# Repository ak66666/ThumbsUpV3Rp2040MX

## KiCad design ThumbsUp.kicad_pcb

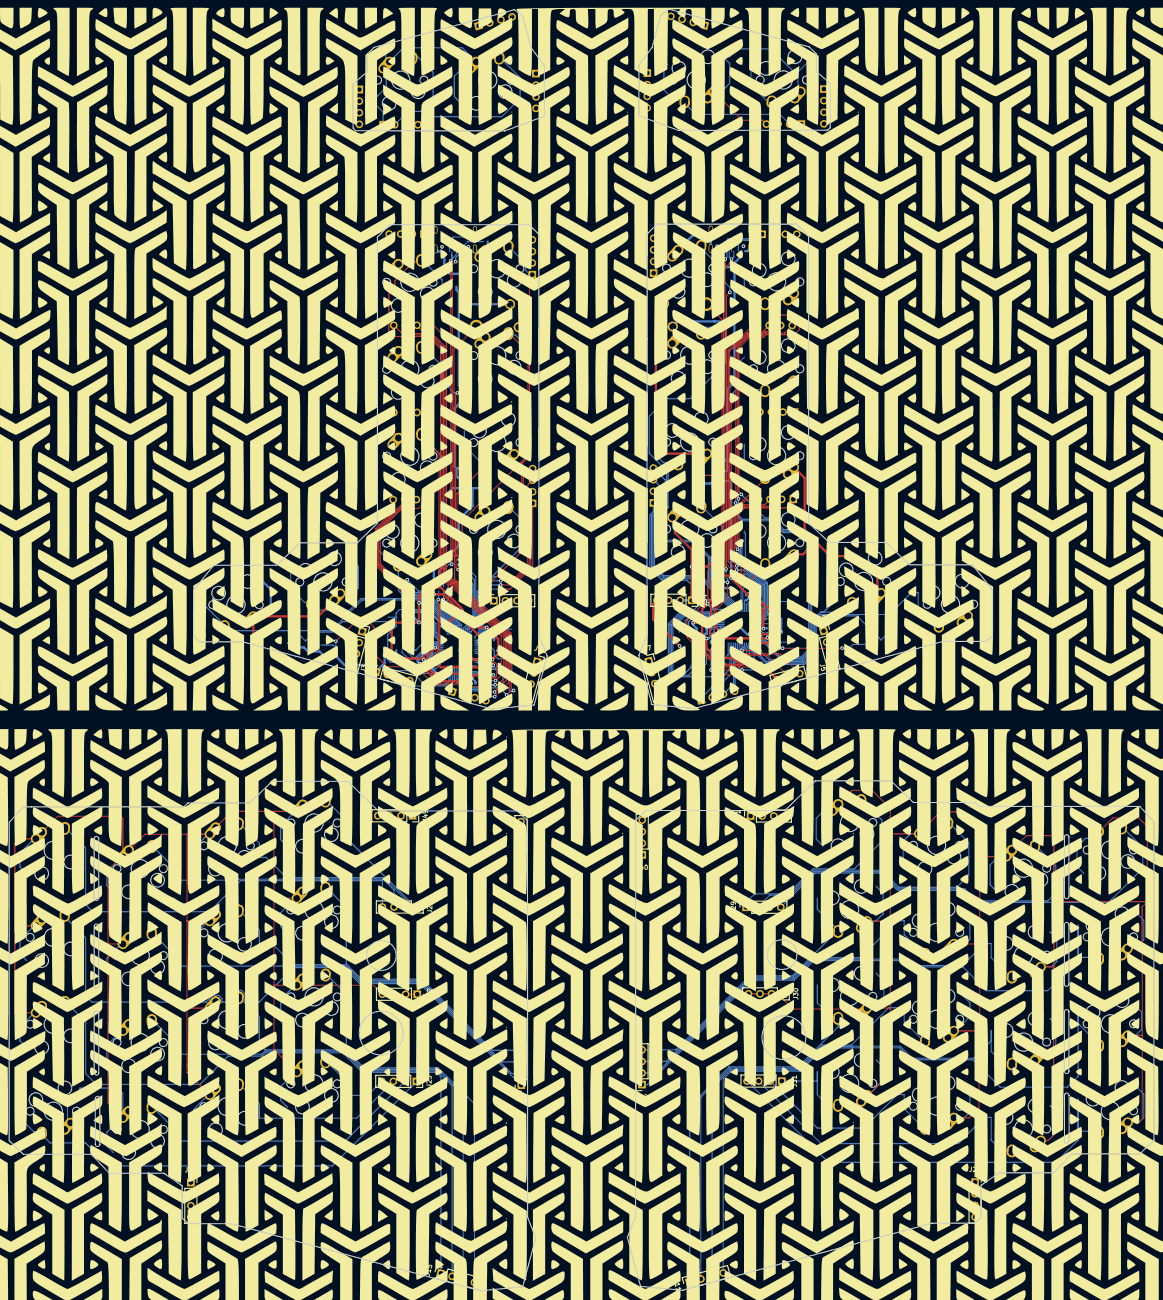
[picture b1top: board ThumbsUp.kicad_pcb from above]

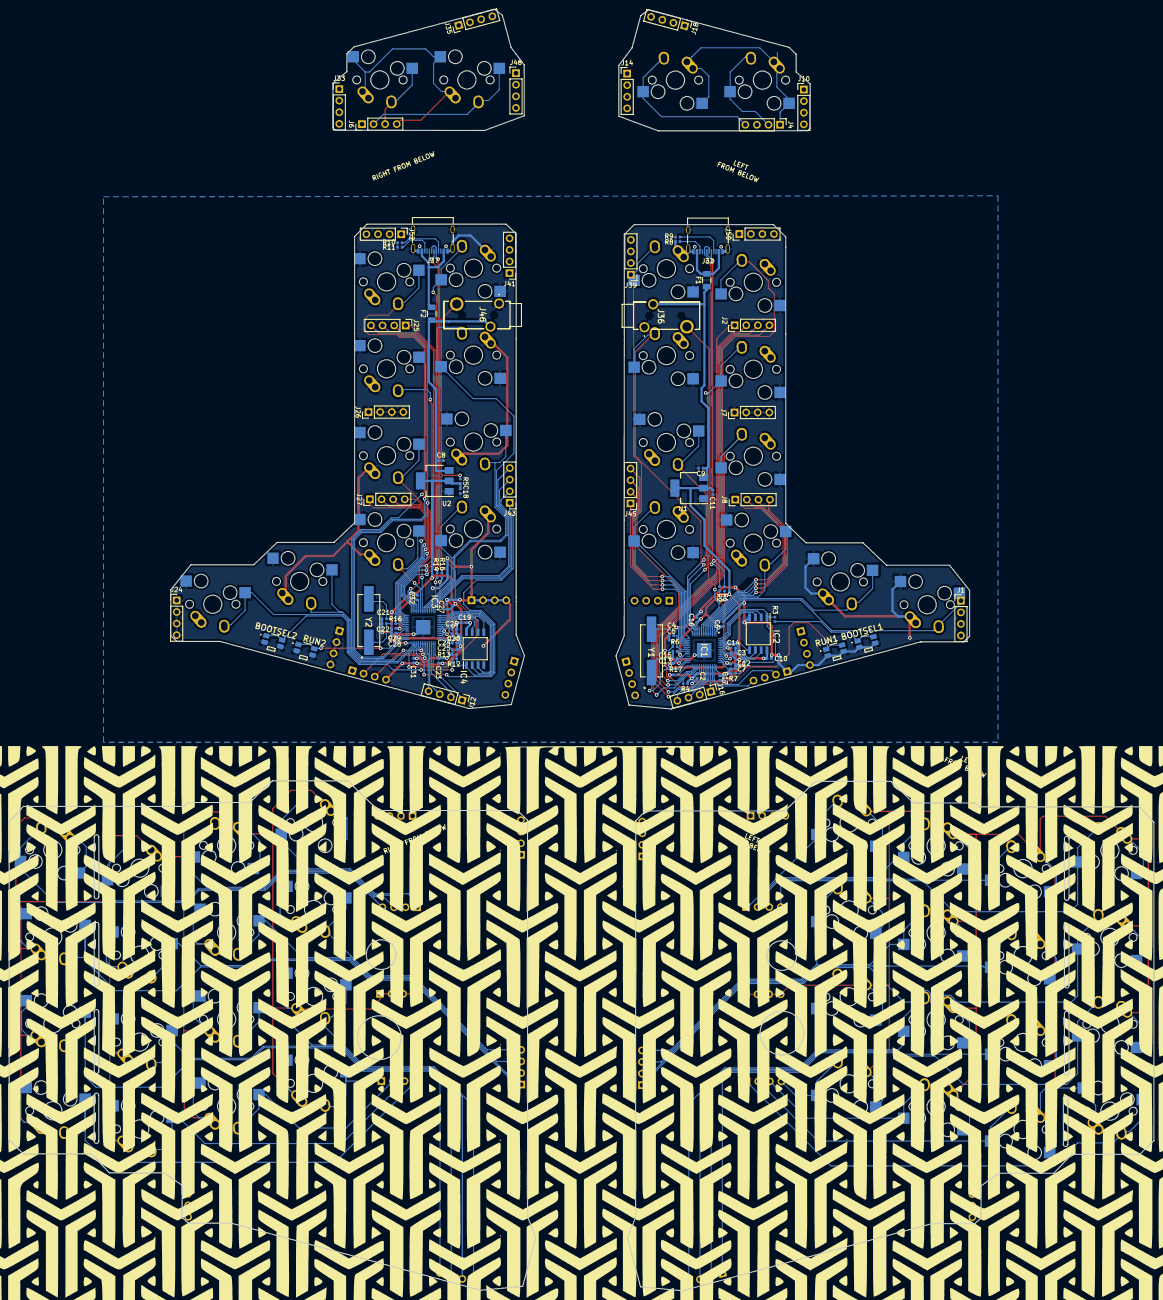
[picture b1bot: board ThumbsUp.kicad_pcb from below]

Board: 2 copper layers, 250.9 x 280.9 mm, 169 parts (89 on the bottom side), 138 nets.

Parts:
BOOTSEL1, BOOTSEL2: TL1016AAF220QG
C2, C6, C7, C10, C13, C14, C15, C16, C17, C19, C23, C25, C26, C27, C28, C29, C31, C32: 0.1uF; C_0402_1005Metric
C3, C12, C20, C24: 1uF; C_0402_1005Metric
C4, C5, C21, C22: 27pF; C_0402_1005Metric
C8, C9, C11, C18: 10uF; C_0402_1005Metric
F1, F2: Polyfuse; Fuse_1206_3216Metric
IC1, IC3: RP2040; QFN40P700X700X90-57N-D
IC2, IC4: W25Q128JVSIM; SOIC127P790X216-8N
J1, J2, J4, J6, J7, J8, J24, J25, J26, J27: Conn_01x04_Male; PinHeader_1x04_P2.54mm_Vertical
J3, J5, J20, J21, J22, J23, J28, J29, J30, J31: Conn_01x04_Female; PinSocket_1x04_P2.54mm_Vertical
J9, J11, J13, J15, J17, J19, J34, J38, J40, J42, J44, J47, J49, J51: Raiser_Female; PinSocket_1x04_P2.54mm_Vertical
J10, J12, J14, J16, J18, J33, J35, J39, J41, J43, J45, J48, J50, J52: Raiser_Male; PinHeader_1x04_P2.54mm_Vertical
J32, J37: USB_C_Receptacle_USB2.0; USB_C_Receptacle_Palconn_UTC16-G
J36, J46: STX-3501-3N; STX35013N
MX1: SwESC; MX-1U-NoLED_HotSwap
MX2: SwTAB; MX-1U-NoLED_HotSwap
MX3: SwLCTL; MX-1U-NoLED_HotSwap
MX4: SwQ; MX-1U-NoLED_HotSwap
MX5: SwA; MX-1U-NoLED_HotSwap
MX6: SwZ; MX-1U-NoLED_HotSwap
MX7: SwW; MX-1U-NoLED_HotSwap
MX8: SwS; MX-1U-NoLED_HotSwap
MX9: SwX; MX-1U-NoLED_HotSwap
MX10: SwLWIN; MX-1U-NoLED_HotSwap
MX11: SwE; MX-1U-NoLED_HotSwap
MX12: SwD; MX-1U-NoLED_HotSwap
MX13: SwC; MX-1U-NoLED_HotSwap
MX14: SwLALT; MX-1U-NoLED_HotSwap
MX15: SwR; MX-1U-NoLED_HotSwap
MX16: SwF; MX-1U-NoLED_HotSwap
MX17: SwV; MX-1U-NoLED_HotSwap
MX18: SwLMOD; MX-1U-NoLED_HotSwap
MX19: SwT; MX-1U-NoLED_HotSwap
MX20: SwG; MX-1U-NoLED_HotSwap
MX21: SwB; MX-1U-NoLED_HotSwap
MX22: SwLSHFT; MX-1U-NoLED_HotSwap
MX23: SwY; MX-1U-NoLED_HotSwap
MX24: SwH; MX-1U-NoLED_HotSwap
MX25: SwN; MX-1U-NoLED_HotSwap
MX26: SwRSHFT; MX-1U-NoLED_HotSwap
MX27: SwU; MX-1U-NoLED_HotSwap
MX28: SwJ; MX-1U-NoLED_HotSwap
MX29: SwM; MX-1U-NoLED_HotSwap
MX30: SwRMOD; MX-1U-NoLED_HotSwap
MX31: SwI; MX-1U-NoLED_HotSwap
MX32: SwK; MX-1U-NoLED_HotSwap
MX33: SwCOMMA; MX-1U-NoLED_HotSwap
MX34: SwRALT; MX-1U-NoLED_HotSwap
MX35: SwO; MX-1U-NoLED_HotSwap
MX36: SwL; MX-1U-NoLED_HotSwap
MX37: SwDOT; MX-1U-NoLED_HotSwap
MX38: SwMENU; MX-1U-NoLED_HotSwap
MX39: SwP; MX-1U-NoLED_HotSwap
MX40: SwCOLON; MX-1U-NoLED_HotSwap
MX41: Sw?; MX-1U-NoLED_HotSwap
MX42: SwBKSP; MX-1U-NoLED_HotSwap
MX43: SwENTER; MX-1U-NoLED_HotSwap
MX44: SwRCTRL; MX-1U-NoLED_HotSwap
MX45: SwGrave; MX-1U-NoLED_HotSwap
MX46: Sw1; MX-1U-NoLED_HotSwap
MX47: Sw2; MX-1U-NoLED_HotSwap
MX48: Sw3; MX-1U-NoLED_HotSwap
MX49: Sw4; MX-1U-NoLED_HotSwap
MX50: Sw5; MX-1U-NoLED_HotSwap
MX51: Sw6; MX-1U-NoLED_HotSwap
MX52: Sw7; MX-1U-NoLED_HotSwap
MX53: Sw8; MX-1U-NoLED_HotSwap
MX54: Sw9; MX-1U-NoLED_HotSwap
MX55: Sw0; MX-1U-NoLED_HotSwap
MX56: SwDEL; MX-1U-NoLED_HotSwap
R1, R2, R14, R15: 27.4; R_0402_1005Metric
R3, R12: 10k; R_0402_1005Metric
R4, R5, R17: 5.1K; R_0402_1005Metric
R6, R16: 1k; R_0402_1005Metric
R7, R13: DNF; R_0402_1005Metric
R8, R9, R10, R11: 5.1k; R_0402_1005Metric
RUN1, RUN2: TL1016AAF220QG
U1, U2: NCP1117-3.3_SOT223; SOT-223-3_TabPin2
Y1, Y2: ABLS-12.000MHZ-B4-T; HC%2f49US-(AT49)_1

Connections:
+1V1: C12.1, C13.1, C14.1, C24.1, C26.1, C28.1, IC1.23, IC1.45, IC1.50, IC3.23, IC3.45, IC3.50
+3V3: C2.1, C3.1, C6.1, C7.1, C10.1, C11.1, C15.1, C16.1, C17.1, C18.1, C19.1, C20.1, C23.1, C25.1, C27.1, C29.1, C31.1, C32.1, IC1.1, IC1.10, IC1.22, IC1.33, IC1.42, IC1.43, IC1.44, IC1.48, IC1.49, IC2.8, IC3.1, IC3.10, IC3.22, IC3.33, IC3.42, IC3.43, IC3.44, IC3.48, IC3.49, IC4.8, R4.1, R5.2, R7.2, R13.2, R17.1, U1.2, U2.2
+5VA: F1.2, F2.2, J32.A4, J32.A9, J32.B4, J32.B9, J37.A4, J37.A9, J37.B4, J37.B9
D+: J32.A6, J32.B6, R2.2
D-: J32.A7, J32.B7, R1.2
K_0: IC3.14, J25.2
K_1: IC1.31, J2.3
K_2: IC1.34, J2.2
K_3: IC1.35, J2.1
K_4: IC1.27, MX49.2
K_5: IC1.28, J39.1, MX50.2
K_6: IC3.12, MX51.2
K_7: IC3.35, MX52.2
K_8: IC3.28, J25.4
K_9: IC3.27, J25.3
K_A: IC1.38, J16.2
K_B: IC1.14, MX21.2
K_BSPC: IC3.34, J43.1
K_C: IC1.5, J8.4
K_COMM: IC3.18, J27.1
K_D: IC1.36, J16.4
K_DEL: IC3.13, J25.1
K_DOT: IC3.17, J27.2
K_E: IC1.15, J45.4
K_ENT: IC3.38, J12.4
K_ESC: IC1.18, J45.1
K_F: IC1.9, MX16.2
K_G: IC1.13, MX20.2
K_GRAVE: IC1.30, J2.4
K_H: IC3.6, MX24.2
K_I: IC3.4, J43.4
K_J: IC3.11, MX28.2
K_K: IC3.41, J12.1
K_L: IC3.40, J12.2
K_LALT: IC1.3, MX14.2
K_LCTL: IC1.8, J8.1
K_LSFT: IC1.41, J3.2
K_LWR: IC3.36, J5.2
K_M: IC3.9, MX29.2
K_MNU: IC3.31, MX38.2
K_N: IC3.7, MX25.2
K_O: IC3.3, J43.3
K_P: IC3.2, J43.2
K_Q: IC1.17, J45.2
K_R: IC1.11, MX15.2
K_RALT: IC3.30, MX34.2
K_RCTL: IC3.15, J27.4
K_RSE: IC1.40, J3.4
K_RSFT: IC3.37, J5.3
K_S: IC1.37, J16.3
K_SEMICOL: IC3.39, J12.3
K_SLASH: IC3.16, J27.3
K_T: IC1.12, MX19.2
K_TAB: IC1.39, J16.1
K_U: IC3.8, MX27.2
K_V: IC1.4, MX17.2
K_W: IC1.16, J45.3
K_WIN: IC1.2, J1.1, MX10.2
K_X: IC1.6, J8.3
K_Y: IC3.5, MX23.2
K_Z: IC1.7, J8.2
L-BASE: BOOTSEL1.3, BOOTSEL1.4, BOOTSEL2.3, BOOTSEL2.4, C2.2, C3.2, C4.2, C5.2, C6.2, C7.2, C8.2, C9.2, C10.2, C11.2, C12.2, C13.2, C14.2, C15.2, C16.2, C17.2, C18.2, C19.2, C20.2, C21.2, C22.2, C23.2, C24.2, C25.2, C26.2, C27.2, C28.2, C29.2, C31.2, C32.2, IC1.19, IC1.57, IC2.4, IC3.19, IC3.29, IC3.57, IC4.4, J3.1, J5.4, J7.1, J7.2, J7.3, J7.4, J9.4, J19.1, J19.2, J19.3, J19.4, J24.1, J24.2, J24.3, J24.4, J26.1, J26.2, J26.3, J26.4, J32.A1, J32.A12, J32.B1, J32.B12, J32.S1, J34.1, J34.2, J34.3, J34.4, J36.1, J37.A1, J37.A12, J37.B1, J37.B12, J37.S1, J46.1, MX10.1, MX14.1, MX15.1, MX16.1, MX17.1, MX19.1, MX20.1, MX21.1, MX23.1, MX24.1, MX25.1, MX27.1, MX28.1, MX29.1, MX34.1, MX38.1, MX49.1, MX50.1, MX51.1, MX52.1, R8.2, R9.1, R10.2, R11.1, RUN1.3, RUN1.4, RUN2.3, RUN2.4, U1.1, U2.1
L-RING1: C8.1, C9.1, F1.1, F2.1, J36.3, J46.3, U1.3, U2.3
L-TIP: IC1.32, J36.2, R4.2
unnamed: BOOTSEL1.1, BOOTSEL1.2, R3.1
unnamed: BOOTSEL2.1, BOOTSEL2.2, R12.1
unnamed: C5.1, R6.2, Y1.1
unnamed: C22.1, R16.2, Y2.1
unnamed: IC1.26, RUN1.1, RUN1.2
unnamed: IC1.29, R17.2
unnamed: IC1.46, R1.1
unnamed: IC1.47, R2.1
unnamed: IC3.26, RUN2.1, RUN2.2
unnamed: IC3.46, R15.1
unnamed: IC3.47, R14.1
unnamed: J4.1, MX18.1, MX22.1
unnamed: J4.2, MX22.2
unnamed: J4.4, MX18.2
unnamed: J6.2, MX30.2
unnamed: J6.3, MX26.2
unnamed: J6.4, MX26.1, MX30.1
unnamed: J11.1, MX32.2
unnamed: J11.2, MX36.2
unnamed: J11.3, MX40.2
unnamed: J11.4, MX43.2
unnamed: J15.1, MX2.2
unnamed: J15.2, MX5.2
unnamed: J15.3, MX8.2
unnamed: J15.4, MX12.2
unnamed: J21.1, MX48.2
unnamed: J21.2, MX47.2
unnamed: J21.3, MX46.2
unnamed: J21.4, MX45.2
unnamed: J22.1, J22.2, J22.3, J22.4, MX1.1, MX2.1, MX3.1, MX4.1, MX5.1, MX6.1, MX7.1, MX8.1, MX9.1, MX11.1, MX12.1, MX13.1, MX45.1, MX46.1, MX47.1, MX48.1
unnamed: J23.1, MX3.2
unnamed: J23.2, MX6.2
unnamed: J23.3, MX9.2
unnamed: J23.4, MX13.2
unnamed: J29.1, MX53.2
unnamed: J29.2, MX54.2
unnamed: J29.3, MX55.2
unnamed: J29.4, MX56.2
unnamed: J30.1, J30.2, J30.3, J30.4, MX31.1, MX32.1, MX33.1, MX35.1, MX36.1, MX37.1, MX39.1, MX40.1, MX41.1, MX42.1, MX43.1, MX44.1, MX53.1, MX54.1, MX55.1, MX56.1
unnamed: J31.1, MX33.2
unnamed: J31.2, MX37.2
unnamed: J31.3, MX41.2
unnamed: J31.4, MX44.2
unnamed: J32.A5, R8.1
unnamed: J32.B5, R9.2
unnamed: J37.A5, R10.1
unnamed: J37.B5, R11.2
unnamed: J42.1, MX42.2
unnamed: J42.2, MX39.2
unnamed: J42.3, MX35.2
unnamed: J42.4, MX31.2
unnamed: J44.1, MX1.2
unnamed: J44.2, MX4.2
unnamed: J44.3, MX7.2
unnamed: J44.4, MX11.2
QSPI_SCLK: IC1.52, IC2.6
QSPI_SD0: IC1.53, IC2.5
QSPI_SD1: IC1.55, IC2.2
QSPI_SD2: IC1.54, IC2.3
QSPI_SD3: IC1.51, IC2.7
QSPI_SSN: IC1.56, IC2.1, R3.2, R7.1
R-TIP: IC3.32, J46.2, R5.1
RD+: J37.A6, J37.B6, R14.2
RD-: J37.A7, J37.B7, R15.2
RQSPI_SCLK: IC3.52, IC4.6
RQSPI_SD0: IC3.53, IC4.5
RQSPI_SD1: IC3.55, IC4.2
RQSPI_SD2: IC3.54, IC4.3
RQSPI_SD3: IC3.51, IC4.7
RQSPI_SSN: IC3.56, IC4.1, R12.2, R13.1
RXIN: C21.1, IC3.20, Y2.2
RXOUT: IC3.21, R16.1
XIN: C4.1, IC1.20, Y1.2
XOUT: IC1.21, R6.1

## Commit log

2023-01-29 Added numbers row to schematics, started PCB modifications
2023-01-29 Enlarged the PCBs, rearranged the raisers.
2023-01-30 Roughed in the lower plates
2023-02-05 Routed R2
2023-02-06 Routing L2
2023-02-10 Routing completed
2023-02-10 Added a raiser near USB connectors
2023-02-10 Minor tracks movements
2023-02-11 Added cuts to break-out the outer columns
2023-02-11 Generated Gerbers, BOMs and POS files
2023-02-11 Fixed a line to close to the holes in L3
2023-02-11 Regenerated Gerbers for the lower PCB
